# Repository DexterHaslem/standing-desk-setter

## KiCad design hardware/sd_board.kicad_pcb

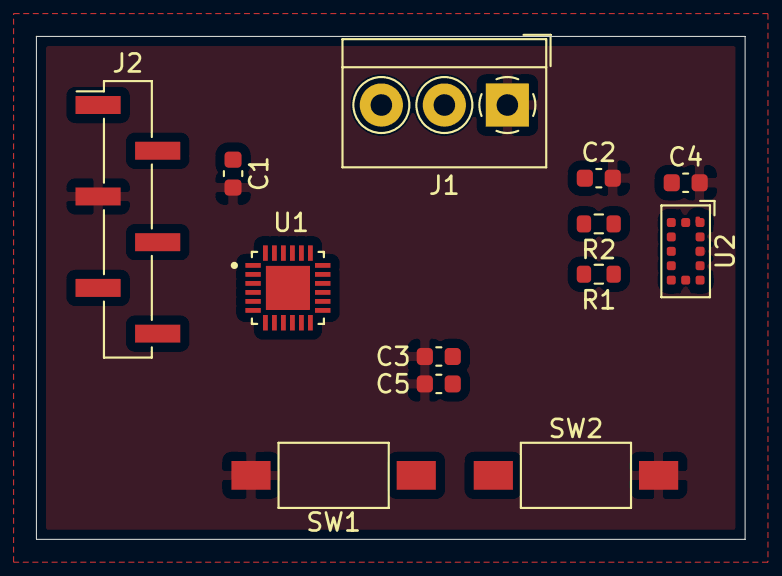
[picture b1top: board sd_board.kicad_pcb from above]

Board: 2 copper layers, 39.4 x 27.9 mm, 13 parts (0 on the bottom side), 4 nets, no tracks yet.

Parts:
C1: 10uF; C_0603_1608Metric
C2, C3: 100nF; C_0603_1608Metric
C4, C5: 4.7uF; C_0603_1608Metric
J1: Screw_Terminal_01x03; TerminalBlock_4Ucon_1x03_P3.50mm_Horizontal
J2: Conn_01x06_Male; PinHeader_1x06_P2.54mm_Vertical_SMD_Pin1Left
R1, R2: 10k; R_0603_1608Metric
SW1, SW2: SW_SPST; SW_SPST_FSMSM
U1: MSP430FR2433IRGER; QFN50P400X400X100-25N
U2: VL53L1CXV0FY1; ST_VL53L1x

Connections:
GND: C1.2, C2.2, C3.2, C4.2, C5.2, J1.1, J2.3, SW1.2, SW2.2, U2.2, U2.3, U2.4, U2.6, U2.12
SCL: R2.1, U2.10
SDA: R1.1, U2.9
VCC: C1.1, C2.1, C3.1, C4.1, C5.1, J2.2, R1.2, R2.2, U2.1, U2.11

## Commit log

2021-07-13 initial, post mcc generation
2021-07-13 buffered eusart interrupts and enable stdio redirect
2021-07-13 mplabx has crashed 3 times already. nevermind
2021-07-13 mplab behaving, housekeeping timers setup
2021-07-13 wake on buttons, sleep 5 sec after idle
2021-07-13 disable sleep at start for now, need to start i2c
2021-07-13 setup i2c. got sensor init and device id coming back correct
2021-07-13 device init complete. forgot to commit files hehe 5am
2021-07-13 fix writing to registers during init, was screwed up. getting distance works
2021-07-13 run device at full 32 MHz
2021-07-13 Create LICENSE
2021-07-13 run i2c at 400kHz. pic manages about 370 at 32MHz
2021-07-13 nm, ranging takes ~65ms, run at 100kHz
2021-07-13 cleanup some more generated xml
2021-07-14 add vl53l1x distance mode and timing budget config:
    this is the absolutely worst I2C interface and 'use'
    of I2C registers i've EVER seen in my entire career
    and by a very large margin. whoever designed the timing
    budget and distance mode registers was not in this
    spacetime we share. VL53L1X is a memorable name
    after all
2021-07-14 forgot, setting distance mode resets timing budget so restore it
2021-07-16 testing fast mode
2021-07-16 move mcu project into its own dir
2021-07-16 start of schematic and pcb
2021-07-20 much better layout, need leds still though
2021-07-20 more pin mapping work on 16LF18346 -
    18313 and 12lf1822 would be hard squeeze (8 pin total)
    setup smore sleep transistion stuff
    use interrupt driven sensor reading
2021-07-20 fix setting shutdown on sensor,
    - timing budget setting lower is not working
    - going higher to eg 500ms works though
2021-07-20 enter sleep at boot, sleep/wake fixes for sensor
2021-07-20 mplabx is 100% unusable:
    10 restarts today trying to get debugging no luck, snap keeps timing out
    and dirt napping in general. something has got even WORSE lately and its
    not my physical setup, I think it's latest mplab and tool packs. tons of
    annoying warnings in console they introduced doesnt introduce confidence
    but at any rate nevermind and FUCK using microchip parts because this
    ide is unusable shit made by idiots.
2021-07-20 rename pic16lf project dir
2021-07-20 updated gitignore for eclipse he he. .
2021-07-20 new msp430fr2433 project..
2021-07-20 start of i2c driver. something is wrong with css 10.4.6 though:
    all projects that use interrupts are getting stuck in __TI_ISR_TRAP,
    including their basic ones with only a single interrupt handler,
    something is up. love how nothing will work for me atm
2021-07-20 well that was painful, RTC is enabled on BOR:
    https://e2e.ti.com/support/microcontrollers/msp-low-power-microcontrollers-group/msp430/f/msp-low-power-microcontroller-forum/720742/msp430fr4133-trying-an-isr-sample-code-msp430fr413x_ta0_01-c-on-cc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
2021-07-20 fix typo in i2c driver. working (but doesnt handle nacks
2021-07-21 port i2c driver. fix stuck on nacks
    drastically more productive in a working ide! who would have thought
    use timera0 ccp0 in count up mode to have a sw delay 1 ms for hacky
    wait timing where needed. not super precise
2021-07-21 add msp430 stuff to hardware. using terrible lib from snapeda, need to fix
2021-07-21 fix committed test i2c addr, smaller bufsizes
2021-07-25 start of ssd1306 driver.. HD44780 displays are pigs
2021-07-25 copy free i2c. caller buffs
2021-07-25 word size counts for i2c indexing, write 1024 display buffer in one go
2021-07-25 ugh, 0x40 display command has to be PER i2c start..
    that stinks, need to change i2c state machine to do 1 write externally,
    or use polling, or adjust buff to have 0x40 in front
2021-07-25 add a way to i2c write across function calls. works but kinda lame
2021-07-25 use 400kHz i2c bus
2021-07-25 fix for transmitting too many bytes in i2c cont write. add pixel
2021-07-25 yeet in some font drawing, enough to move forward
2021-07-25 fix for primitive line wrapping
2021-07-25 add ssd1306 sleep/wake
2021-07-26 first pass of deep sleep mode
2021-07-26 software debounce noisy buttons to prevent i2c bus slams and stuff
2021-08-03 pull out logic stubs forgot to commit
2021-08-04 vl513lx shutdown pin, set int pin input
2021-08-04 write2 data endianness was wrong. discovered in timing budget set, int
2021-08-04 problem was intermeasurement left default 100ms. add api for that
2021-08-04 implement get intermeasurement ms for posterity
2021-08-04 oops, correctly use helpers. inline them as well
2021-08-04 switched to simplier font. testing fast displaying
2021-08-04 testing modes, will need to figure out decent rate for desk speed
2021-08-04 pointless benchmarking to know what im working with
2021-08-04 50ms should be good for moving desk rate
